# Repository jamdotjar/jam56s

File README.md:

# jam56s
A 56-key hotswap column-staggered split keyboard.

*I'll replace this with a proper photo once it's built, but for now heres a quick render*

This is my first custom keyboard design, and my second hardware project. It was designed with a few goals in mind:
1. to be functional ( not broken, hard to break )
2. to be mine ( my own design, for my use case )
3. to be simple ( simple to use, simple to build )
4. to be something I'll actually use.

these were the basis of almost every decision I made while designing this. I chose a split layout because I already had a fairly nice 65% keyboard (the nuPhy air60 v2), I felt like anything too similar would fight for use (4). Secondly, I wanted to try and make a layout very personal to me, so this would be a truly from-scratch build (2). I used [ergopad](https://pashutk.com/ergopad/) to get a rough idea of what a good layout could be for me, then I used [ergogen](https://ergogen.xyz/) to quickly protoype my designs until I arrived at something I could copy in keycad. For the layout and physical design of the jam56s I took inspiration from the [lily58](https://github.com/kata0510/Lily58), the [Corne](https://github.com/foostan/crkbd), and the [ErgoTravel](https://github.com/jpconstantineau/ErgoTravel), among others. My main considerations were having enough keys for macros and modifiers, while not letting it get too big. The final layout is 6x(4-key column) + a 4 key thumb cluster. ( wired as a 7x4 matrix, see below )
wiring.

The board includes:
- Per-key RGB
- 1 I2C breakout ( for an OLED )
- RJ45 split comms
- Hot-swap sockets
I Chose an RJ45 jack over the more common TRRS jack as it can be safely hotplugged while the board is on. I didn't want to have to handle a USBC plug, which also seemed like overkill and ran the risk of frying the keeb if it was used for anything other than split comms.

The case is mostly 3D printed, but you can late lasercut for better asthetics and rigidity. This was my first time using fusion so it's just a little bit jank. It's kinda an open-air sorta sandiwch design, I mainly just wanted to always be able to see the PCB.

## BOM
In case you want to try to build this yourself, here's the prices I got for all the components. Prices are all in USD, even though I'm in Canada. ( also includes shipping )
| Item                            | Quantity | Price      | Source             | Additional details                                                   |
| ------------------------------- | -------- | ---------- | ------------------ | -------------------------------------------------------------------- |
| PCB                             | 2x5      | 39.99      | JLCPCB             | 23.6 subtotal + 12.14 shipping + 4.25 tax                            |
| Plate                           | 2        | 35.67      | SendCutSend        | I Might be able to get it for cheaper locally, or in a diff material |
| Orpheus Pico                    | 2        | N/A        | Hack Club          | Can be replaced with other USCB pico clone                           |
| Kailh hot-swap socket           | 70       | 99c        | Aliexpress         | This is where the welcome deal seems to be placed right now          |
| RJ45 Jacks                      | 2        | 2.63       | Aliexpress         |                                                                      |
| RJ45 cable                      | 1        | 1.72       | Aliexpress         |                                                                      |
| .91 in oled                     | 2.22     | Aliexpress |                    |
| 1n4148 diodes                   | 100      | 1.97       | Aliexpress         |                                                                      |
| 0805 0.1uf capacitor            | 100      | 2.2        | Aliexpress         |                                                                      |
| SK6812mini-Es                   | 100      | 6.26       | Aliexpress         |                                                                      |
| TTC silent red or silent frozen | 60       | 32.7       | TorontoKeyboardMan | <alt pick is otemu silent yellow jade (0.22) or silent kitty (0.45)  |
| Keycaps                         | 140          |20.35            |Aliexpress                    |
| M2.5 x 25mm screw               | 50       | 2.28       | Aliexpress         |                                                                      |
| M2.5x9mm spacer                 | 35       | 2.78       | Aliexpres          | can also be 3d printed                                               |
| Total                           | 1 | 149.54 | ||

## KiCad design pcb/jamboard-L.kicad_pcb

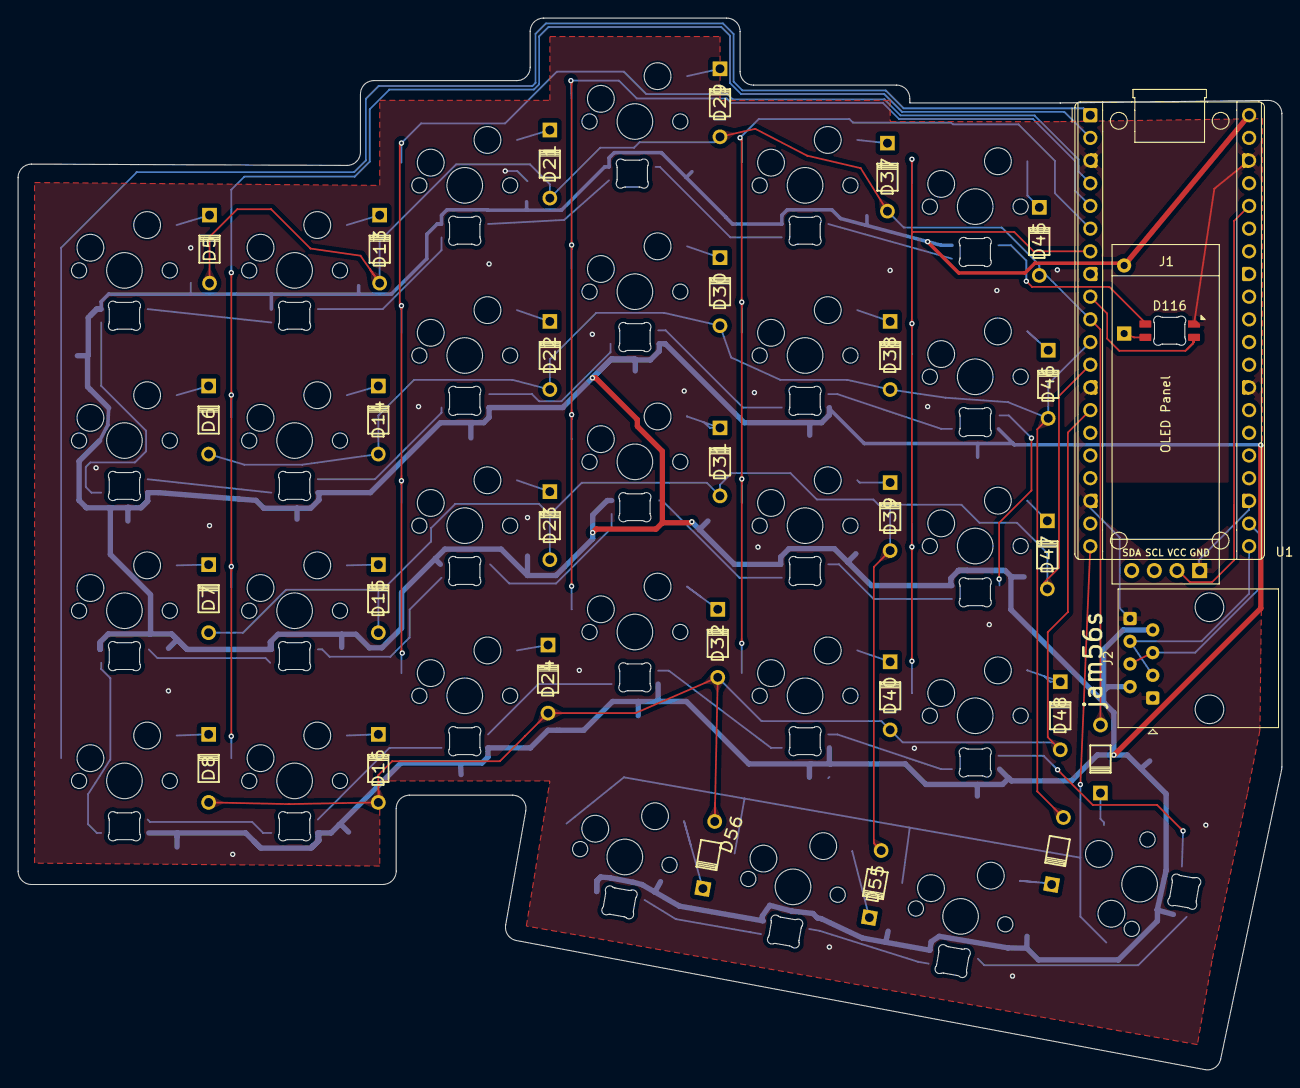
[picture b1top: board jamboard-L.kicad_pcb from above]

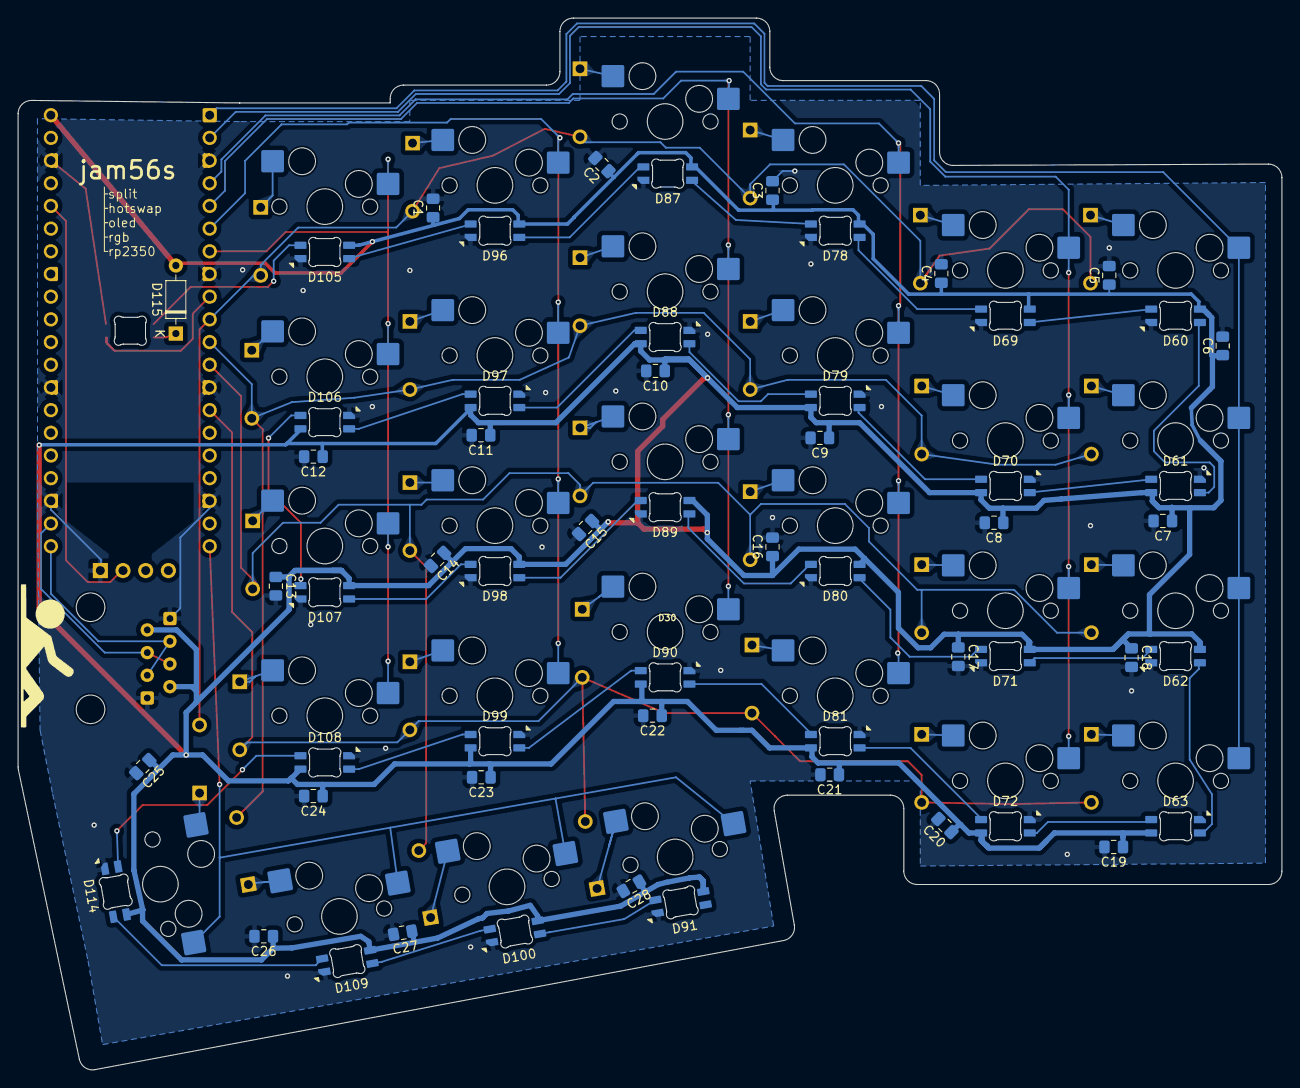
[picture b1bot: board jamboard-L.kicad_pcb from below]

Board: 2 copper layers, 141.4 x 117.7 mm, 117 parts (85 on the bottom side), 74 nets.

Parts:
C1, C2, C3, C4, C5, C6, C7, C8, C9, C10, C11, C12, C13, C14, C15, C16, C17, C18, C19, C20, C21, C22, C23, C24, C25, C26, C27, C28: C; C_0805_2012Metric_Pad1.18x1.45mm_HandSolder
D5, D6, D7, D8, D13, D14, D15, D16, D21, D22, D23, D24, D29, D30, D31, D32, D37, D38, D39, D40, D45, D46, D47, D48, D53, D54, D55, D56: D; Diode
D60, D61, D62, D63, D69, D70, D71, D72, D78, D79, D80, D81, D87, D88, D89, D90, D91, D96, D97, D98, D99, D100, D105, D106, D107, D108, D109, D114, D116: SK6812MINI; LED_6028R
D115: 1N4148; D_DO-35_SOD27_P7.62mm_Horizontal
J1: OLED_128x32; SSD1306-0.91-OLED-4pin-128x32
J2: RJ45; RJ45_Amphenol_54602-x08_Horizontal
S5, S6, S7, S8, S13, S14, S15, S16, S21, S22, S23, S24, S29, S30, S31, S32, S37, S38, S39, S40, S45, S46, S47, S48, S54, S55, S56: SW_Push_45deg; MX-Hotswap-1U
S53: SW_Push_45deg; MX-Hotswap-1.75U
U1: Pico; RaspberryPi_Pico_Common_THT

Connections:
+3V3: J1.2 (VCC), U1.36 (3V3)
+5V: C1.1, C2.1, C3.1, C4.1, C5.1, C6.1, C7.1, C8.1, C9.1, C10.1, C11.1, C12.1, C13.1, C14.1, C15.1, C16.1, C17.1, C18.1, C19.1, C20.1, C21.1, C22.1, C23.1, C24.1, C25.1, C26.1, C27.1, C28.1, D60.1 (VDD), D61.1 (VDD), D62.1 (VDD), D63.1 (VDD), D69.1 (VDD), D70.1 (VDD), D71.1 (VDD), D72.1 (VDD), D78.1 (VDD), D79.1 (VDD), D80.1 (VDD), D81.1 (VDD), D87.1 (VDD), D88.1 (VDD), D89.1 (VDD), D90.1 (VDD), D91.1 (VDD), D96.1 (VDD), D97.1 (VDD), D98.1 (VDD), D99.1 (VDD), D100.1 (VDD), D105.1 (VDD), D106.1 (VDD), D107.1 (VDD), D108.1 (VDD), D109.1 (VDD), D114.1 (VDD), D115.2 (A), J2.2, J2.7, U1.40 (VBUS)
GND: C1.2, C2.2, C3.2, C4.2, C5.2, C6.2, C7.2, C8.2, C9.2, C10.2, C11.2, C12.2, C13.2, C14.2, C15.2, C16.2, C17.2, C18.2, C19.2, C20.2, C21.2, C22.2, C23.2, C24.2, C25.2, C26.2, C27.2, C28.2, D60.4 (VSS), D61.4 (VSS), D62.4 (VSS), D63.4 (VSS), D69.4 (VSS), D70.4 (VSS), D71.4 (VSS), D72.4 (VSS), D78.4 (VSS), D79.4 (VSS), D80.4 (VSS), D81.4 (VSS), D87.4 (VSS), D88.4 (VSS), D89.4 (VSS), D90.4 (VSS), D91.4 (VSS), D96.4 (VSS), D97.4 (VSS), D98.4 (VSS), D99.4 (VSS), D100.4 (VSS), D105.4 (VSS), D106.4 (VSS), D107.4 (VSS), D108.4 (VSS), D109.4 (VSS), D114.4 (VSS), D116.4 (VSS), J1.1 (GND), J2.1, J2.8, U1.3 (GND), U1.8 (GND), U1.13 (GND), U1.18 (GND), U1.23 (GND), U1.28 (GND), U1.38 (GND)
LED_DATA_L: D116.3 (DIN), U1.9 (GPIO6)
LinkA_L: J2.3, J2.6, U1.21 (GPIO16)
LinkB_L: J2.4, J2.5, U1.22 (GPIO17)
MATRIX COL 0: S5.1, S6.1, S7.1, S8.1, U1.1 (GPIO0)
MATRIX COL 1: S13.1, S14.1, S15.1, S16.1, U1.2 (GPIO1)
MATRIX COL 2: S21.1, S22.1, S23.1, S24.1, U1.4 (GPIO2)
MATRIX COL 3: S29.1, S30.1, S31.1, S32.1, U1.5 (GPIO3)
MATRIX COL 4: S37.1, S38.1, S39.1, S40.1, U1.6 (GPIO4)
MATRIX COL 5: S45.1, S46.1, S47.1, S48.1, U1.7 (GPIO5)
MATRIX COL 6: S53.1, S54.1, S55.1, S56.1, U1.20 (GPIO15)
MATRIX ROW 0: D5.1 (K), D13.1 (K), D21.1 (K), D29.1 (K), D37.1 (K), D45.1 (K), D53.1 (K), U1.10 (GPIO7)
MATRIX ROW 1: D6.1 (K), D14.1 (K), D22.1 (K), D30.1 (K), D38.1 (K), D46.1 (K), D54.1 (K), U1.11 (GPIO8)
MATRIX ROW 2: D7.1 (K), D15.1 (K), D23.1 (K), D31.1 (K), D39.1 (K), D47.1 (K), D55.1 (K), U1.12 (GPIO9)
MATRIX ROW 3: D8.1 (K), D16.1 (K), D24.1 (K), D32.1 (K), D40.1 (K), D48.1 (K), D56.1 (K), U1.14 (GPIO10)
unnamed: D5.2 (A), S5.2
unnamed: D6.2 (A), S6.2
unnamed: D7.2 (A), S7.2
unnamed: D8.2 (A), S8.2
unnamed: D13.2 (A), S13.2
unnamed: D14.2 (A), S14.2
unnamed: D15.2 (A), S15.2
unnamed: D16.2 (A), S16.2
unnamed: D21.2 (A), S21.2
unnamed: D22.2 (A), S22.2
unnamed: D23.2 (A), S23.2
unnamed: D24.2 (A), S24.2
unnamed: D29.2 (A), S29.2
unnamed: D30.2 (A), S30.2
unnamed: D31.2 (A), S31.2
unnamed: D32.2 (A), S32.2
unnamed: D37.2 (A), S37.2
unnamed: D38.2 (A), S38.2
unnamed: D39.2 (A), S39.2
unnamed: D40.2 (A), S40.2
unnamed: D45.2 (A), S45.2
unnamed: D46.2 (A), S46.2
unnamed: D47.2 (A), S47.2
unnamed: D48.2 (A), S48.2
unnamed: D53.2 (A), S53.2
unnamed: D54.2 (A), S54.2
unnamed: D55.2 (A), S55.2
unnamed: D56.2 (A), S56.2
unnamed: D60.3 (DIN), D69.2 (DOUT)
unnamed: D60.2 (DOUT), D61.3 (DIN)
unnamed: D61.2 (DOUT), D70.3 (DIN)
unnamed: D62.3 (DIN), D71.2 (DOUT)
unnamed: D62.2 (DOUT), D63.3 (DIN)
unnamed: D63.2 (DOUT), D72.3 (DIN)
unnamed: D69.3 (DIN), D78.2 (DOUT)
unnamed: D70.2 (DOUT), D79.3 (DIN)
unnamed: D71.3 (DIN), D80.2 (DOUT)
unnamed: D72.2 (DOUT), D81.3 (DIN)
unnamed: D78.3 (DIN), D87.2 (DOUT)
unnamed: D79.2 (DOUT), D88.3 (DIN)
unnamed: D80.3 (DIN), D89.2 (DOUT)
unnamed: D81.2 (DOUT), D90.3 (DIN)
unnamed: D87.3 (DIN), D96.2 (DOUT)
unnamed: D88.2 (DOUT), D97.3 (DIN)
unnamed: D89.3 (DIN), D98.2 (DOUT)
unnamed: D90.2 (DOUT), D99.3 (DIN)
unnamed: D100.3 (DIN), D109.2 (DOUT)
unnamed: D91.3 (DIN), D100.2 (DOUT)
unnamed: D105.3 (DIN), D116.2 (DOUT)
unnamed: D96.3 (DIN), D105.2 (DOUT)
unnamed: D97.2 (DOUT), D106.3 (DIN)
unnamed: D106.2 (DOUT), D107.3 (DIN)
unnamed: D98.3 (DIN), D107.2 (DOUT)
unnamed: D99.2 (DOUT), D108.3 (DIN)
unnamed: D108.2 (DOUT), D114.3 (DIN)
unnamed: D109.3 (DIN), D114.2 (DOUT)
unnamed: D115.1 (K), D116.1 (VDD)

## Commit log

2025-06-12 inital commit
2025-06-17 worked on readme
2025-06-20 added firmware folder
2025-06-20 remove erroneous file
2025-06-22 added firmware properly
2025-06-22 finialized BOM
2025-10-27 added BOM.csv
2025-10-27 rust firmware attempt1
2025-10-27 Update README.md
    Updated BOM section to clarify that prices include shipping.
2025-11-08 organzied production assets
